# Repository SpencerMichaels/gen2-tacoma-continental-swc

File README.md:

# Gen 2 Tacoma → Continental steering-wheel controls

A small board that lets the steering-wheel audio buttons of a **second-generation Toyota Tacoma** (2005–2015) control a **Continental CRD4512UBA** aftermarket radio.

The Tacoma's wheel buttons and the Continental's steering-wheel input both use resistance, but they aren't compatible. The truck splits its seven buttons across two wires (SW1 and SW2), with resistances of about 0 Ω, 330 Ω, 1 kΩ and 3.1 kΩ on each. The radio reads a single wire and recognises a different set of resistance ranges, from 0–100 Ω for Volume Down to 1.3–3 kΩ for Mic Mute. This board reads the truck's two lines, works out which button is pressed, and switches in the resistance the radio wants for that command.

*3D render, seen from the connector edge. J1 (grey) is a simplified stand-in model. The XIAO module itself isn't shown, only its two sockets.*

## How it works

- **Inputs.** Each wheel line (SW1, SW2) is pulled up to 3.3 V through 2.2 kΩ. Pressing a button connects a resistor from the line to ground, and the voltage drops by a predictable amount. The XIAO RP2040 reads both lines with its 12-bit ADC about every 2 ms.
- **Decoding.** Each reading falls into a band: released, or one of the buttons. Readings between bands, or both lines active at once, are treated as invalid and the output is released. A press has to hold steady for 20 ms before it counts.
- **Outputs.** Five resistors (47 Ω, 191 Ω, 390 Ω, 1 kΩ, 2 kΩ) sit between the radio's SWRC+ and SWRC GND, each switched by its own MOSFET. Five of the seven commands use one resistor; Volume + and Seek + use two in parallel, switched on together in a single register write. While you hold a button, the board holds the resistance; the radio handles its own repeat.
- **Power.** The board runs from the truck's switched 12 V ACC through a fuse, a reverse-polarity diode, a 10 Ω resistor, a TVS diode and an LT3012 regulator set to 5 V. It draws about 25 mA. The radio supplies its own sense voltage, so the board never drives the radio input; it only presents a resistance.
- **Fail-safe.** Gate pull-downs hold every output off through reset or with the XIAO unplugged. A 1-second watchdog restarts a stalled loop, and a press held longer than 10 seconds is released.

| Wheel button | Line | Radio command | Board output |
|---|---|---|---:|
| Seek + | SW1 | Seek Up | 390 Ω ‖ 1 kΩ = 281 Ω |
| Seek − | SW1 | Seek Down | 390 Ω |
| Volume + | SW1 | Volume Up | 191 Ω ‖ 390 Ω = 128 Ω |
| Volume − | SW1 | Volume Down | 47 Ω |
| Mode | SW2 | Source | 191 Ω |
| Answer (off-hook) | SW2 | Phone (answers, or ends an active call) | 1 kΩ |
| Hang Up (on-hook) | SW2 | Mic Mute | 2 kΩ |

The radio's Phone command toggles with the call state, so Answer covers both answering and hanging up. That frees the Hang Up button for Mic Mute. The radio has a Preset command (470–720 Ω) that isn't mapped to any button.

The wheel resistances, the radio's measured recognition windows and the harness wiring are in [docs/interface.md](docs/interface.md).

## Status

**Built and working on the bench.** Two boards were made with factory assembly. On a powered CRD4512UBA, every command acted once per press: Volume Up/Down, Source, Seek Up/Down, Mic Mute (toggled on and off during a call), and Phone (ended a connected call). Powered from 12 V ACC, the board draws 25 mA and the regulator stays cool.

The ADC bands for the wheel buttons come from the Toyota service-manual resistances and circuit simulation, not from readings on the truck. If a button misbehaves in your truck, send `status` over USB while holding it, and compare the count with the bands in [firmware/README.md](firmware/README.md).

Tested with a 2013 Tacoma. The wheel resistances are documented for 2011–2015 trucks; earlier Gen 2 trucks with audio buttons probably match, but measure them first.

## Building one

1. **Order the assembled board.** The regulator (LT3012, 3 × 4 mm DFN) and most of the parts are surface-mount, so a PCB assembly service is the practical route. Upload [`hardware/fab/tacoma_swc_gerbers.zip`](hardware/fab/tacoma_swc_gerbers.zip), [`BOM.csv`](hardware/fab/BOM.csv) and [`smt-placement.csv`](hardware/fab/assembly/smt-placement.csv). See the [ordering notes](hardware/fab/ORDERING.md).
2. **Get a XIAO RP2040** (the standard one, not the Plus) with its 1 × 7 male headers soldered on. It plugs into two sockets on the carrier.
3. **Load the firmware.** Pull the **JP1** shunt first, then hold the XIAO's BOOT button while plugging in USB and copy a UF2 file onto the drive that appears: [`tacoma-swc-bench.uf2`](firmware/releases/tacoma-swc-bench.uf2) to test from a computer, or [`tacoma-swc-vehicle.uf2`](firmware/releases/tacoma-swc-vehicle.uf2) for the truck. Details in [firmware/README.md](firmware/README.md).
4. **Test on the bench (optional).** With the bench build, USB serial commands like `volume_up` pulse the matching output for 300 ms. Connect J1 pin 9 (SWRC+) and pin 10 (SWRC GND) to the radio and check each one.
5. **Print the case** (PETG or ASA) from [`hardware/enclosure/`](hardware/enclosure/): two parts, no supports, 4 × M3 × 12 screws, no nuts.

6. **Install.** Load the vehicle build, **refit JP1**, plug the harness into J1, and set the radio's SWRC type to *Resistance*.

## Wiring

J1 is a Molex Micro-Fit 3.0, 2 × 6 right-angle header (43045-1209). It mates with the 12-pin harness of an Axxess AXSWC steering-wheel interface, so the board can take the AXSWC's place. You don't need the AXSWC module itself, only its harness:

- **Alternative:** the [RED WOLF 20-pin steering-wheel control harness w/RCA](https://www.amazon.com/RED-WOLF-Replacement-2003-2014-Aftermarket/dp/B09S33B8L1). It's sold separately as a replacement harness for the AXSWC/ASWC-1, so it has the same 12-pin plug and pinout. It should work as-is, though it hasn't been tried with this board yet.
- **Make your own:** a Molex 43025-1200 housing and Micro-Fit crimp terminals.

| J1 pin | Signal | Goes to |
|---:|---|---|
| 4 | SW1 | Tacoma radio connector R15-21 (wheel ladder 1) |
| 8 | SW2 | Tacoma R15-22 (wheel ladder 2) |
| 6 | GND | Vehicle ground, tied to the wheel's SWG (R15-23) |
| 12 | ACC | Switched 12 V |
| 9 | SWRC+ | Radio steering-wheel input, 3.5 mm plug tip (red) |
| 10 | SWRC GND | Radio steering-wheel ground (white) |
| others | — | Not connected |

Test points: TP1 GND, TP2 5 V regulator output, TP3 SWRC+, TP4 SWRC GND, TP5 ACC after protection, TP6 XIAO 5 V, TP7/TP8 SW1/SW2 at the ADC, TP9 3.3 V.

## Safety notes

- **Pull JP1 before plugging in USB.** The XIAO's 5 V pin is wired straight to its USB VBUS. With JP1 fitted, the board's regulator and the computer's USB port would be connected together. The silkscreen says so too.
- Don't measure the board's output resistance with an ohmmeter while the radio is connected and powered. Watch what the radio does instead.
- The power input is fused, reverse-protected and clamped (24 V TVS), but it hasn't been qualified against automotive load-dump or jump-start tests.
- Don't wrap the case in harness tape; leave the vented side and the top open.

## Repository layout

| Path | What |
|---|---|
| [`hardware/`](hardware/) | KiCad 10 project, design checks, SPICE simulation and the generator scripts. [Design notes](hardware/README.md). |
| [`hardware/fab/`](hardware/fab/) | Gerbers, BOM, placement files, assembly drawings, [ordering notes](hardware/fab/ORDERING.md) |
| [`hardware/enclosure/`](hardware/enclosure/) | Case STLs and STEP, plus the FreeCAD generator script |
| [`firmware/`](firmware/) | RP2040 firmware (PlatformIO + Arduino-Pico), prebuilt UF2 files, host tests |
| [`docs/interface.md`](docs/interface.md) | The Tacoma wheel ladders, the Continental input, and the harness |

## License

- **Hardware** (everything under `hardware/` except the Python scripts: schematic, PCB, Gerbers, BOM, case models): [CERN-OHL-S-2.0](LICENSE-HARDWARE).
- **Firmware, scripts and tools:** [GPL-3.0](LICENSE).
- **Documentation:** follows the hardware or software it describes.

## Credits

- Steering-wheel resistances come from the 2013 Tacoma repair manual: *Navigation System (Diagnostic Codes & Symptom Tests) → Symptom Tests → Steering Pad Switch Circuit → Procedure*. The harness and switch-assembly resistance tables are under Figures 45 and 46. [docs/interface.md](docs/interface.md#tacoma-steering-wheel) has the full citation.
- The XIAO socket footprint follows Seeed Studio's [KiCad library](https://github.com/Seeed-Studio/OPL_Kicad_Library).
- Built with KiCad, Freerouting, ngspice, FreeCAD, PlatformIO and the [Arduino-Pico](https://github.com/earlephilhower/arduino-pico) core.

Toyota and Tacoma are trademarks of Toyota Motor Corporation. Continental is a trademark of its owner. Axxess is a trademark of Metra Electronics. XIAO is a trademark of Seeed Technology. This project isn't affiliated with or endorsed by any of them.

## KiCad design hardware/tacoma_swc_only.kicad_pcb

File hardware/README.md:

# Hardware

The KiCad 10 project for the SWC board: 65 × 55 mm, 2 layers, 1.6 mm FR-4, ENIG, all components on the top side. Most parts are SMT and meant for factory assembly; the XIAO RP2040 plugs into two sockets.

| File | What |
|---|---|
| `tacoma_swc_only.kicad_pro` / `.kicad_sch` / `.kicad_pcb` | The KiCad project, with four schematic sheets: interface, power, inputs, outputs |
| `fab/` | Gerbers, BOM, placement files, assembly drawings, [ordering notes](fab/ORDERING.md) |
| `enclosure/` | 3D-printable case: STL, STEP and the generator; see its [README](enclosure/README.md) |
| `checks/` | Schematic PDF, layout PDF, top/bottom SVGs, ERC/DRC reports, design-check results, netlist, simulation outputs |
| `design_intent.json`, `output_commands.json`, `parts_selection.json` | Machine-readable pin, net, command and part data that the scripts and firmware tests check against |
| `build_schematic.py`, `build_board.py`, `clean_route_stubs.py`, `check_design.py` | Scripts that generate and check the design (see [Rebuilding](#rebuilding)) |
| `simulation/`, [`simulation_review.md`](simulation_review.md) | ngspice checks of the inputs, outputs, command transitions and layout spacing |
| `footprints/`, `Tacoma.kicad_sym` | Project footprint and symbol libraries |
| `3dmodels/` | Simplified Micro-Fit (J1) model and its generator, since KiCad's library has none |

**Status.** This is the board that was built: the PCB file's SHA-256 was `6188309d…cdaf1a` when it was fabricated. Since then only the 3D model references for J1 and A1 have changed, so copper, DRC and Gerbers are the same. It passes ERC (0 violations) and DRC with schematic parity (0 violations, 0 unconnected, 0 parity errors). Two factory-assembled boards were bench-tested with the radio; see the [main README](../README.md#status).

## Circuit

| Block | Parts | What it does |
|---|---|---|
| **Power input** | F1 250 mA fast fuse, D1 STPS1H100A, R1 10 Ω 1 W, D2 SMBJ24A, C1 47 µF/63 V, C2 10 µF/63 V | ACC → fuse → reverse-blocking Schottky → 10 Ω → TVS clamp. R1 limits the current the TVS has to absorb. |
| **Regulator** | U1 LT3012EDE (DFN-12), R2 30.1 k / R3 10.0 k (0.1 %), C3 22 µF polymer | 5 V nominal (4.97 V). The LT3012 tolerates reverse input and up to 80 V. The output goes to the XIAO's 5 V pin through JP1. |
| **JP1** | 2-pin header + shunt | Disconnects the regulator from the XIAO. **Pull it before connecting USB**: the XIAO's 5 V pin is tied directly to USB VBUS. |
| **Wheel inputs** | D5/D6 BAS70, R5/R6 2.2 kΩ, R7/R8 22 kΩ, C5/C6 10 nF, D7/D8 BAS70-04, R4 330 Ω | Each line is pulled up from the XIAO's 3.3 V through a diode and 2.2 kΩ. The 22 kΩ + 10 nF filter and the clamp diodes protect the ADC pin. R4 bleeds 3.3 V so that small clamp currents can't lift the rail. |
| **Outputs** | Q1/Q3/Q5/Q6/Q7 AO3400A, R11 47 Ω, R13 191 Ω, R15 390 Ω, R16 1 kΩ, R17 2 kΩ (1 %), 1 kΩ gate resistors, 100 kΩ gate pull-downs | Five low-side branches from SWRC+ to SWRC GND. The pull-downs keep every branch off while the XIAO is in reset or unplugged. |
| **C11** | 10 nF | Across SWRC+ / SWRC GND. Softens the switching edges. |
| **NT1** | net tie | Bonds SWRC GND to the board ground. |

### XIAO pins

The firmware uses RP2040 GPIO numbers, not the XIAO's D labels.

| Carrier pad | XIAO label | RP2040 | Function |
|---:|---|---|---|
| 1 | D0 | GP26 / ADC0 | SW1 |
| 2 | D1 | GP27 / ADC1 | SW2 |
| 7 | D6 | GP0 | 47 Ω branch (Q1) |
| 8 | D7 | GP1 | 191 Ω branch (Q3) |
| 9 | D8 | GP2 | 390 Ω branch (Q5) |
| 10 | D9 | GP4 | 1 kΩ branch (Q6) |
| 11 | D10 | GP3 | 2 kΩ branch (Q7) |
| 12 | 3V3 | | Pull-up and clamp supply (from the XIAO's own regulator) |
| 13 | GND | | |
| 14 | 5V | | From JP1 |
| 3–6 | D2–D5 | | Not used |

Pads are numbered DIP-style: viewed from above with USB at the top, 1–7 run down the left side and 8–14 run up the right.

### Command masks

| Command | Branches | Ω | GPIO mask |
|---|---|---:|---:|
| Release | none | open | `0x00` |
| Volume Down | Q1 | 47 | `0x01` |
| Volume Up | Q3 + Q5 | 128.2 | `0x06` |
| Source | Q3 | 191 | `0x02` |
| Seek Up | Q5 + Q6 | 280.6 | `0x14` |
| Seek Down | Q5 | 390 | `0x04` |
| Phone | Q6 | 1000 | `0x10` |
| Mic Mute | Q7 | 2000 | `0x08` |

## Power budget

| | |
|---|---|
| Measured, 12 V ACC, XIAO running, no USB | 25 mA total |
| Measured, 12 V ACC, XIAO removed | under 1 mA |
| Design allocation | 60 mA |
| U1 dissipation at 16 V, 25 mA | about 0.3 W (U1 plus R1) |

At the measured current, U1, C3 and R1 aren't noticeably warm. The case has vents over U1 and R1 anyway.

## PCB layout

- **Placement.** J1 is on the top edge, and the XIAO sits on the left with its USB port facing up. The output bank runs along the bottom, and the power section is on the right. There's an M3 mounting hole in each corner, with a 7 × 7 mm copper keep-out around each.
- **Routing.** Freerouting, imported into KiCad and cleaned up. Signals are 0.3 mm; ACC and the SWRC return are 0.6 mm. There are ground pours on both layers. U1's exposed pad has four ground vias.
- **ACC spacing.** `tacoma_swc_only.kicad_dru` keeps at least 2 mm between every ACC net and SWRC+ or the output-branch nets; the layout gives about 2.15 mm. So a stray solder bridge is unlikely to put 12 V on the radio's input.
- **XIAO sockets.** The two Samtec SSW-107-01-G-S sockets are 15.24 mm apart in 1.04 mm finished holes. Nothing on the carrier sits under the module.
- **3D models.**
  - J1 uses `3dmodels/Molex_Micro-Fit_3.0_43045-1210_simplified.step`, generated by `3dmodels/make_microfit_model.py`.
  - A1 uses two of KiCad's `PinSocket_1x07_P2.54mm_Vertical` models. There's no model of the XIAO module itself.

## Simulation

`simulation/run_simulation.py` builds ngspice circuits from the KiCad netlist. Results are in `checks/simulation/`, and the summary is in [`simulation_review.md`](simulation_review.md). The checks cover:

- **Input bands:** every wheel resistance over the tolerance sweep lands in its own band.
- **Outputs:** every command lands inside its Continental window.
- **Transitions:** all 56 command-to-command changes, at two C11 values (`check_command_transitions.py`).
- **Firmware:** 3,024 cases with the real C++ decoder driven by simulated ADC waveforms, including bounce and RC settling (`check_firmware_integration.py`).
- **Faults:** an ACC bridge onto SWRC+, and a drain-source short.

The MCU and radio are modelled as simple stubs, so these results show the design is consistent, not that it survives every fault.

## Rebuilding

Run from the repository root:

```sh
KPY=/Applications/KiCad/KiCad.app/Contents/Frameworks/Python.framework/Versions/Current/bin/python3

python3 hardware/check_design.py                             # pin/net/part checks → checks/design_checks.json
python3 hardware/simulation/run_simulation.py                # ngspice (needs ngspice on PATH)
python3 hardware/simulation/check_command_transitions.py
python3 hardware/simulation/check_firmware_integration.py
$KPY hardware/simulation/audit_layout.py                     # ACC spacing audit

kicad-cli sch erc --format json -o hardware/checks/erc.json hardware/tacoma_swc_only.kicad_sch
kicad-cli pcb drc --schematic-parity --format json -o hardware/checks/pcb-drc.json hardware/tacoma_swc_only.kicad_pcb
```

`build_schematic.py` and `build_board.py` generated the original schematic and placement. **Re-running them overwrites the KiCad files**, including the routing. Edit the KiCad files directly instead, unless you mean to start over.

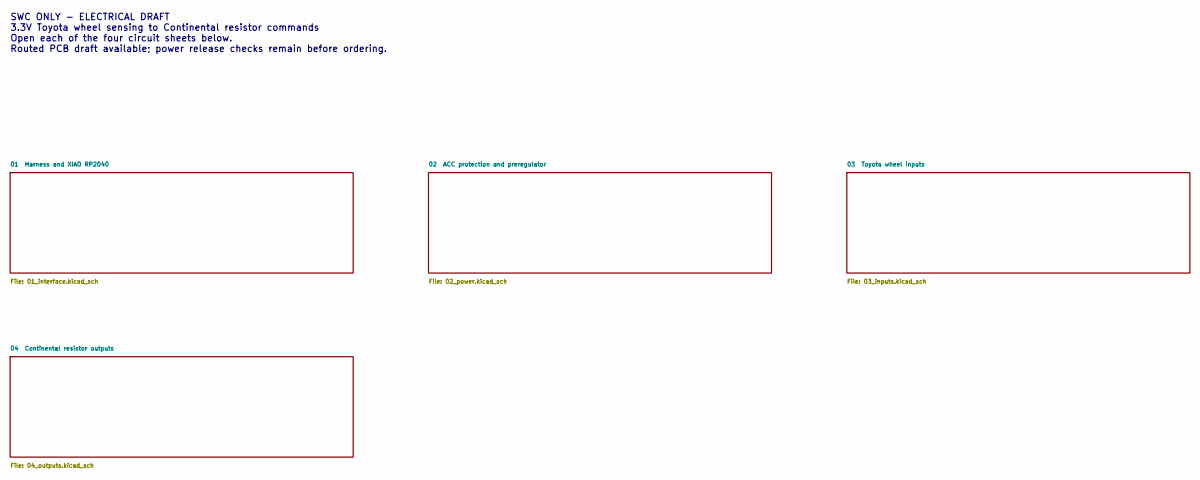
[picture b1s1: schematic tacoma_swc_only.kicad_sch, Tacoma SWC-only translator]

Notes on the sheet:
SWC ONLY - ELECTRICAL DRAFT 3.3V Toyota wheel sensing to Continental resistor commands Open each of the four circuit sheets below. Routed PCB draft available; power release checks remain before ordering.

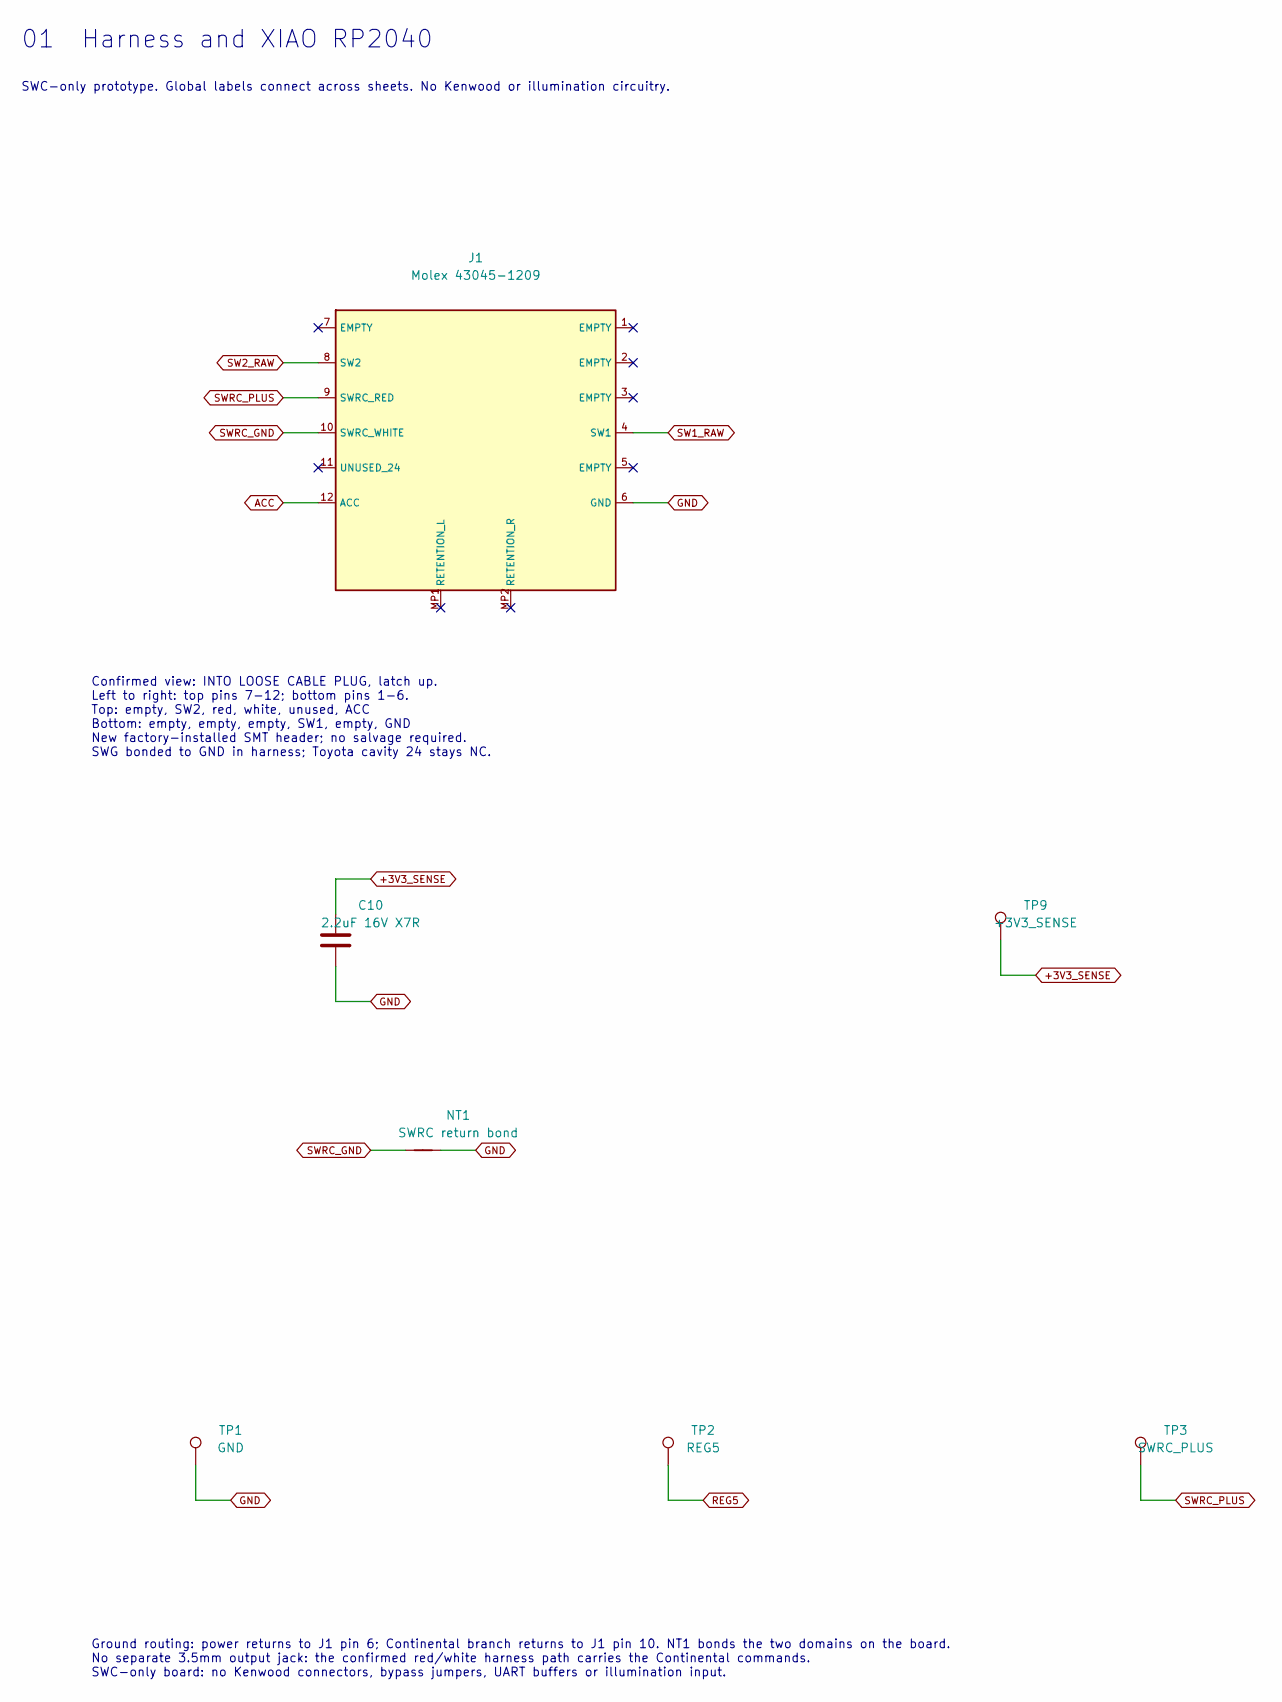
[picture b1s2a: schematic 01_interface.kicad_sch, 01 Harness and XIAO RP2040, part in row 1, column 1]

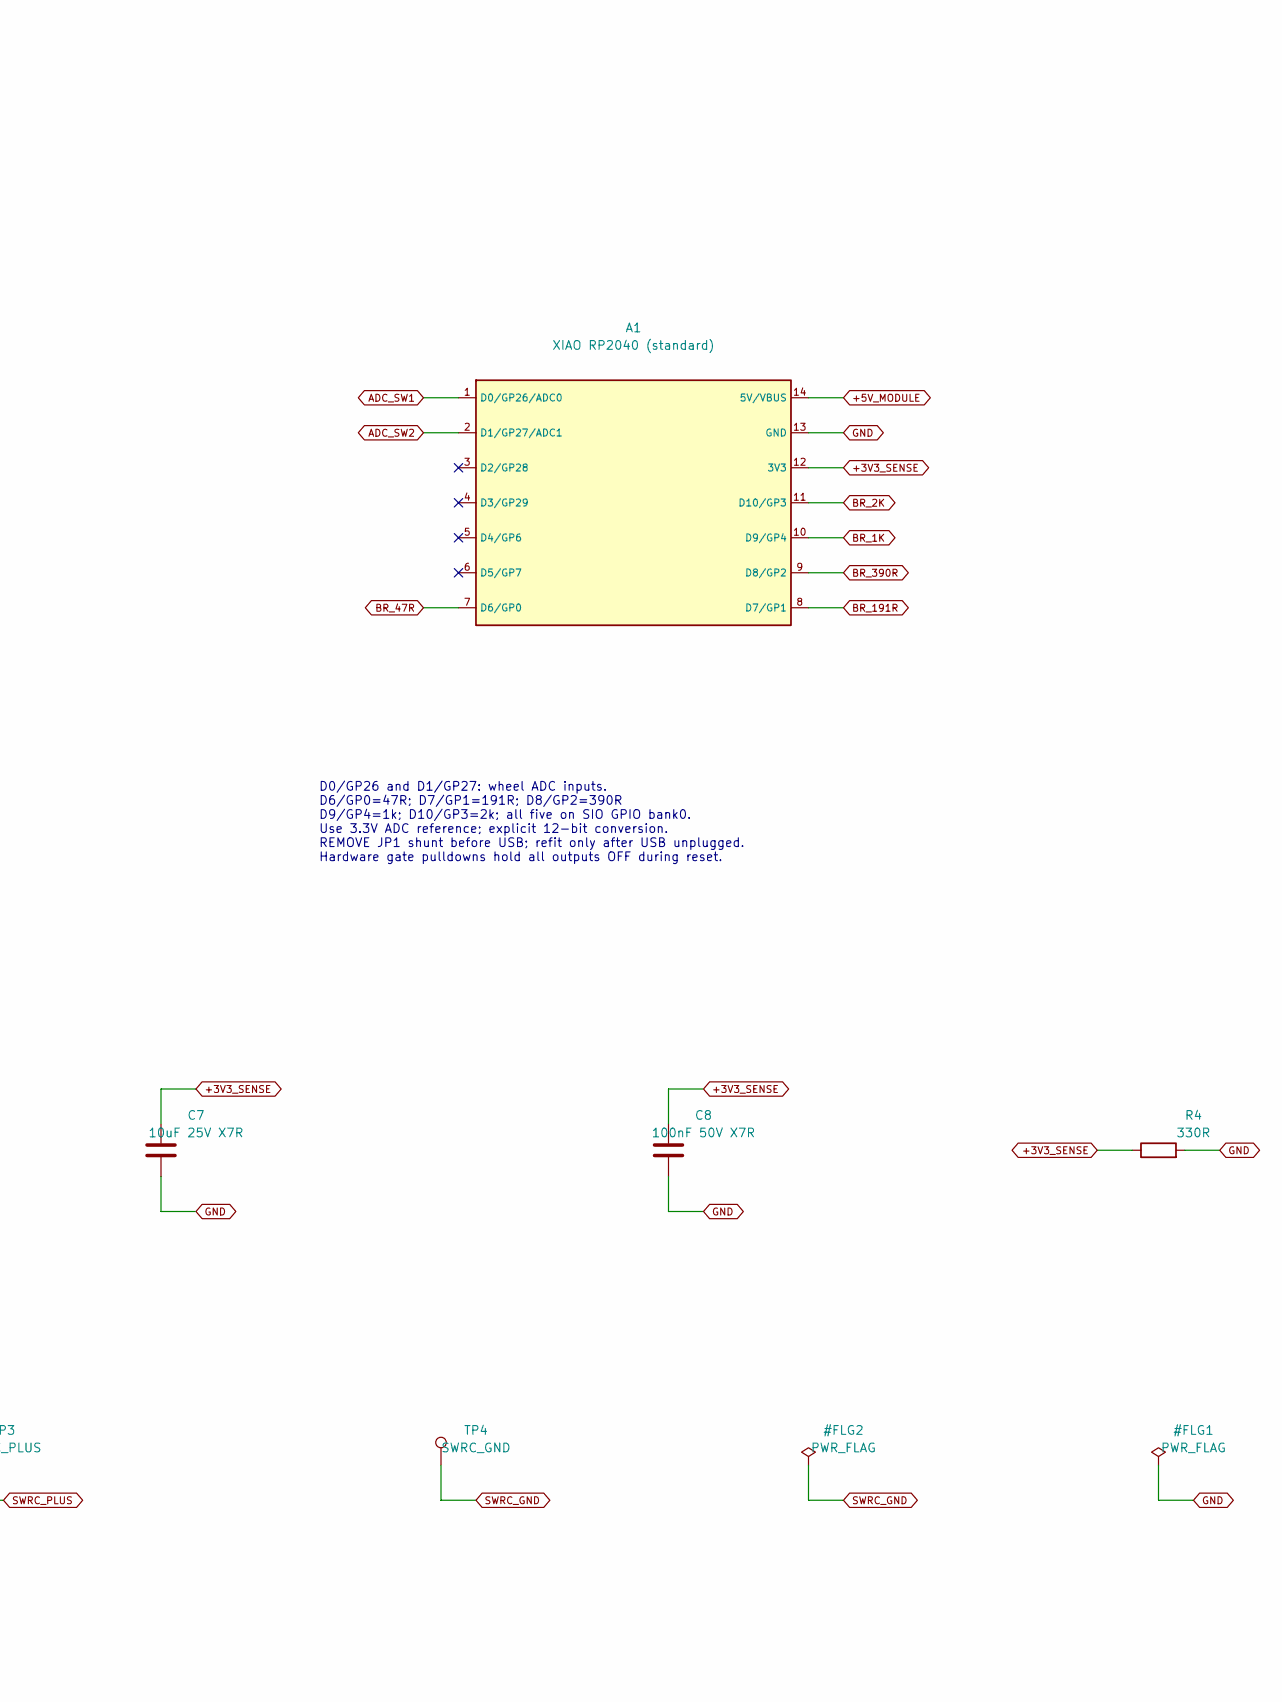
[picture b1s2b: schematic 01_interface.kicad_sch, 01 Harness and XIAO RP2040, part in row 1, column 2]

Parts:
A1: XIAO RP2040 (standard); XIAO_RP2040_Socket_2x7; MPN 102010428
C7: 10uF 25V X7R; C_1206_3216Metric; MPN GRM31CR71E106KA12L
C8: 100nF 50V X7R; C_0805_2012Metric; MPN C0805C104K5RACTU
C10: 2.2uF 16V X7R; C_0805_2012Metric; MPN GRM21BR71C225KA12L
J1: Molex 43045-1209; Molex_43045_12_SMT_SeparateRetentionPads; MPN 43045-1209
NT1: SWRC return bond; NetTie-2_SMD_Pad2.0mm
R4: 330R; R_1206_3216Metric; MPN RC1206FR-07330RL
TP1: GND; TestPoint_Pad_D1.5mm
TP2: REG5; TestPoint_Pad_D1.5mm
TP3: SWRC_PLUS; TestPoint_Pad_D1.5mm
TP4: SWRC_GND; TestPoint_Pad_D1.5mm
TP9: +3V3_SENSE; TestPoint_Pad_D1.5mm

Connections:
+3V3_SENSE: A1.12 (3V3), C7.1, C8.1, C10.1, R4.1, TP9.1; also elsewhere on the board
+5V_MODULE: A1.14 (5V/VBUS); also elsewhere on the board
ACC: J1.12 (ACC); also elsewhere on the board
ADC_SW1: A1.1 (D0/GP26/ADC0); also elsewhere on the board
ADC_SW2: A1.2 (D1/GP27/ADC1); also elsewhere on the board
BR_1K: A1.10 (D9/GP4); also elsewhere on the board
BR_2K: A1.11 (D10/GP3); also elsewhere on the board
BR_47R: A1.7 (D6/GP0); also elsewhere on the board
BR_191R: A1.8 (D7/GP1); also elsewhere on the board
BR_390R: A1.9 (D8/GP2); also elsewhere on the board
GND: A1.13 (GND), C7.2, C8.2, C10.2, J1.6 (GND), NT1.2, R4.2, TP1.1; also elsewhere on the board
REG5: TP2.1; also elsewhere on the board
SW1_RAW: J1.4 (SW1); also elsewhere on the board
SW2_RAW: J1.8 (SW2); also elsewhere on the board
SWRC_GND: J1.10 (SWRC_WHITE), NT1.1, TP4.1; also elsewhere on the board
SWRC_PLUS: J1.9 (SWRC_RED), TP3.1; also elsewhere on the board

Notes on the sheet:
01 Harness and XIAO RP2040
SWC-only prototype. Global labels connect across sheets. No Kenwood or illumination circuitry.
Confirmed view: INTO LOOSE CABLE PLUG, latch up. Left to right: top pins 7-12; bottom pins 1-6. Top: empty, SW2, red, white, unused, ACC Bottom: empty, empty, empty, SW1, empty, GND New factory-installed SMT header; no salvage required. SWG bonded to GND in harness; Toyota cavity 24 stays NC.
D0/GP26 and D1/GP27: wheel ADC inputs. D6/GP0=47R; D7/GP1=191R; D8/GP2=390R D9/GP4=1k; D10/GP3=2k; all five on SIO GPIO bank0. Use 3.3V ADC reference; explicit 12-bit conversion. REMOVE JP1 shunt before USB; refit only after USB unplugged. Hardware gate pulldowns hold all outputs OFF during reset.
Ground routing: power returns to J1 pin 6; Continental branch returns to J1 pin 10. NT1 bonds the two domains on the board. No separate 3.5mm output jack: the confirmed red/white harness path carries the Continental commands. SWC-only board: no Kenwood connectors, bypass jumpers, UART buffers or il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

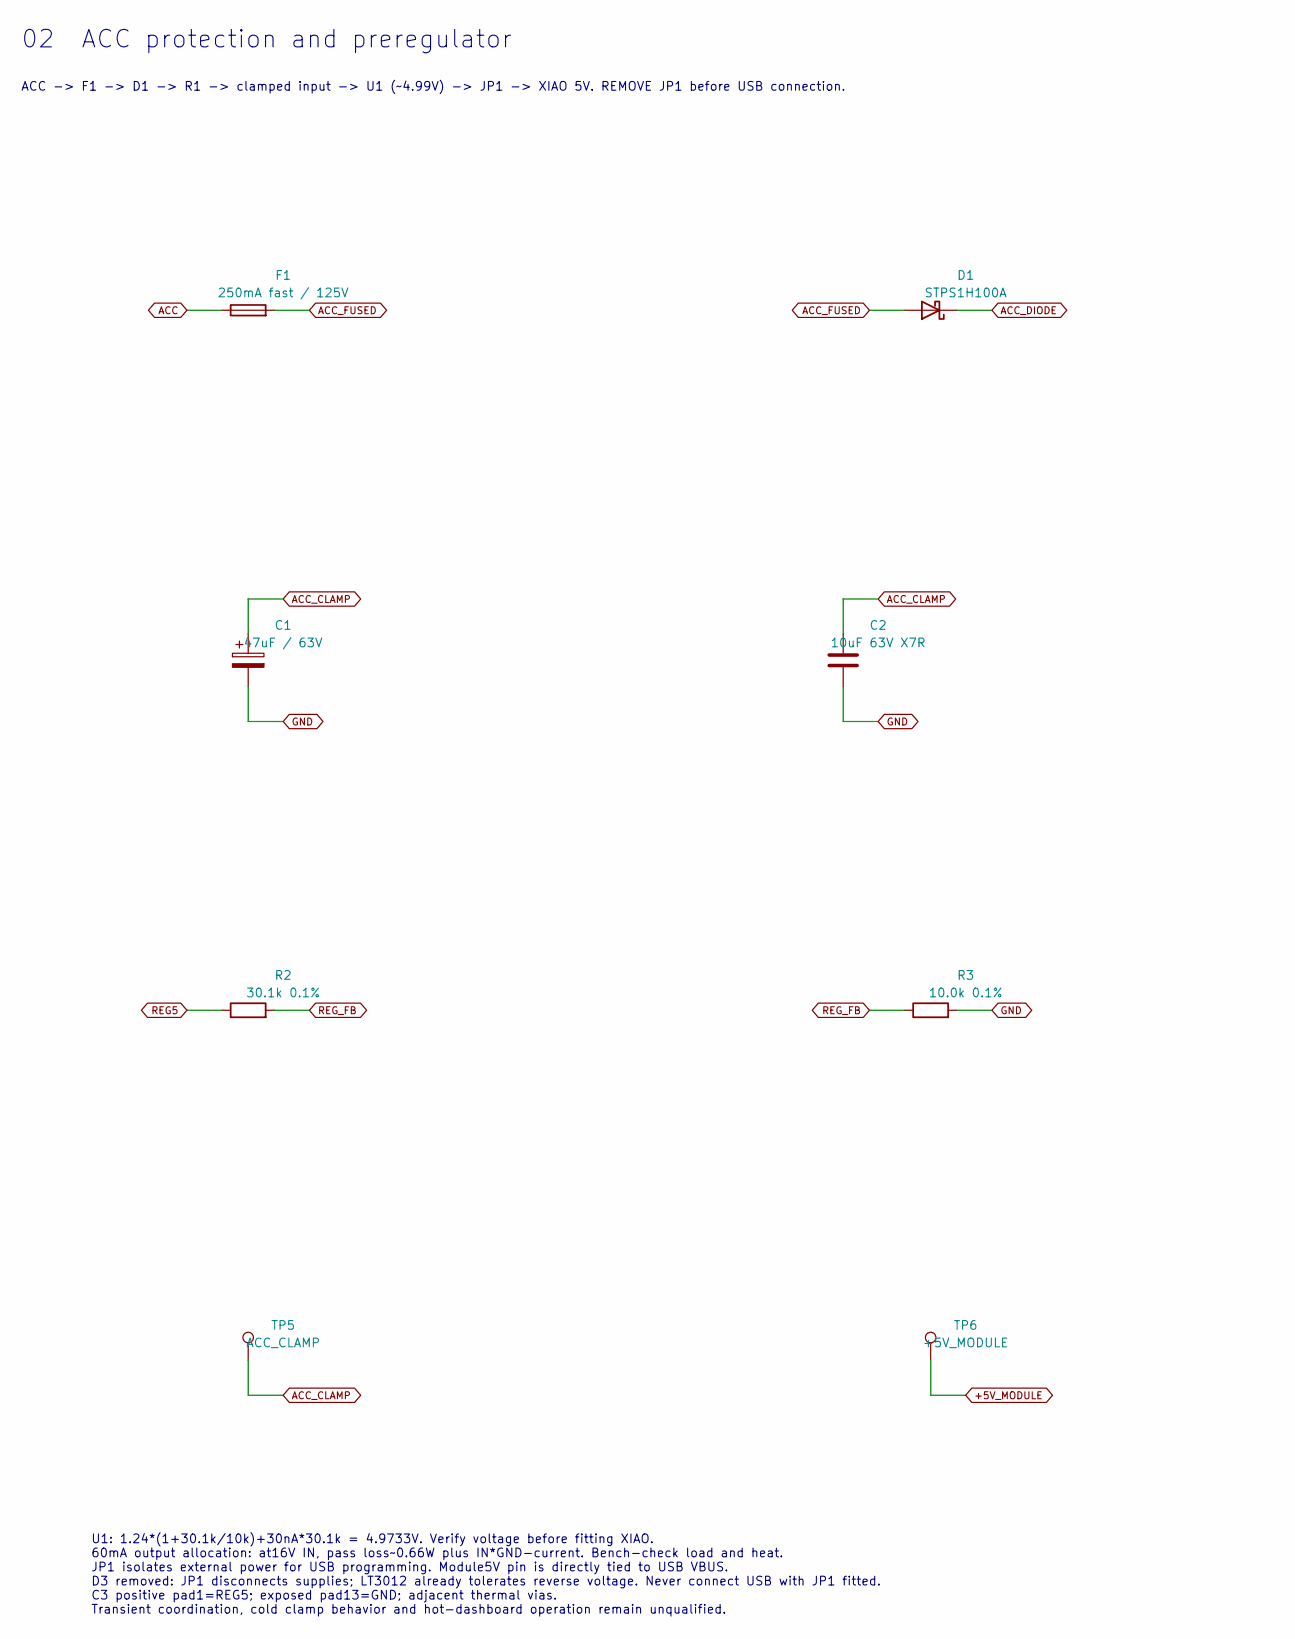
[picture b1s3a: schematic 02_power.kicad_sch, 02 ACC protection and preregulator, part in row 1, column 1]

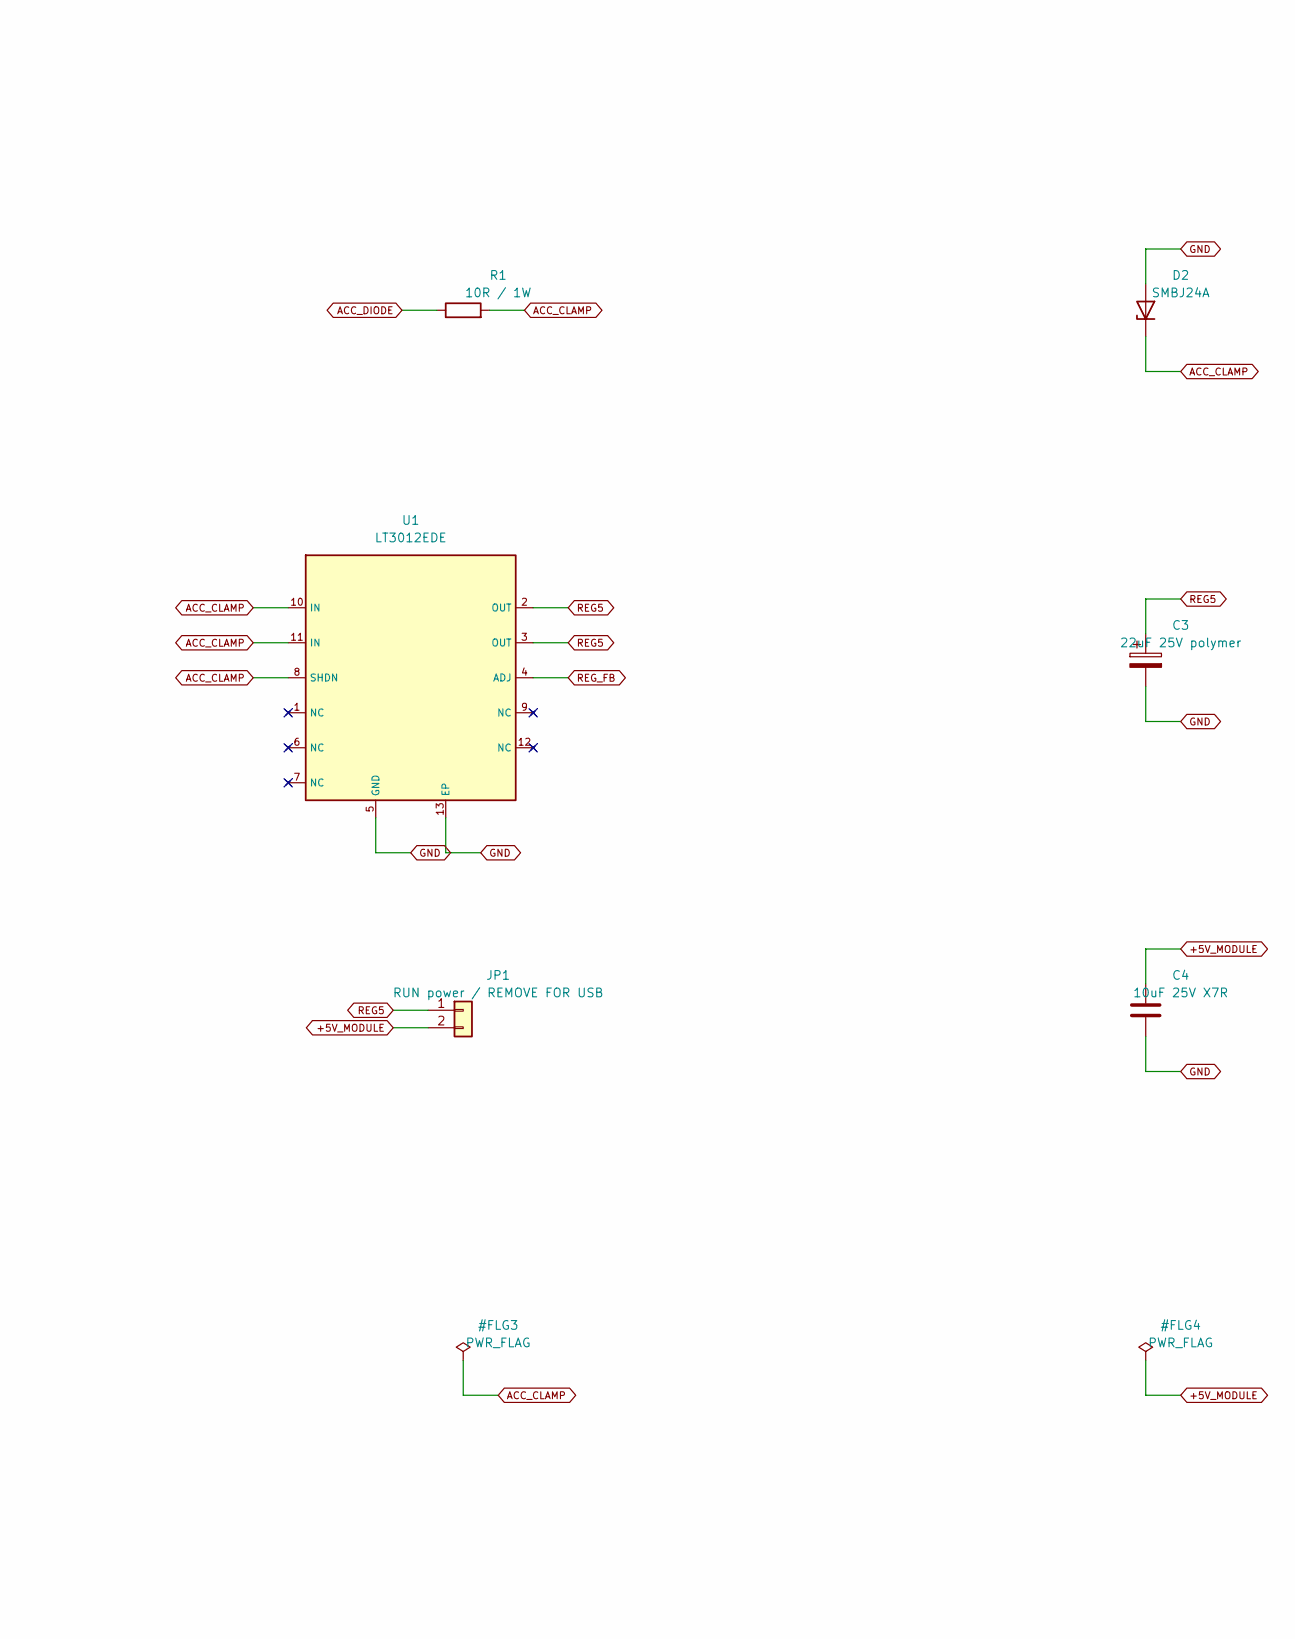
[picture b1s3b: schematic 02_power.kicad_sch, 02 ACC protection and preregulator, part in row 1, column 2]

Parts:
C1: 47uF / 63V; CP_Elec_8x10.5; MPN EEE-FK1J470P
C2: 10uF 63V X7R; C_1210_3225Metric; MPN GRM32ER71J106KA12L
C3: 22uF 25V polymer; CP_EIA-3528-21_Kemet-B; MPN TCJB226M025R0100E
C4: 10uF 25V X7R; C_1206_3216Metric; MPN GRM31CR71E106KA12L
D1: STPS1H100A; D_SMA; MPN STPS1H100A
D2: SMBJ24A; D_SMB; MPN SMBJ24A
F1: 250mA fast / 125V; Littelfuse_451_6.1x2.69mm; MPN 0451.250MRL
JP1: RUN power / REMOVE FOR USB; PinHeader_1x02_P2.54mm_Vertical; MPN TSW-102-07-G-S
R1: 10R / 1W; R_Axial_DIN0414_L11.9mm_D4.5mm_P20.32mm_Horizontal; MPN AC01000001009JA100
R2: 30.1k 0.1%; R_0805_2012Metric; MPN RT0805BRD0730K1L
R3: 10.0k 0.1%; R_0805_2012Metric; MPN RT0805BRD0710KL
TP5: ACC_CLAMP; TestPoint_Pad_D1.5mm
TP6: +5V_MODULE; TestPoint_Pad_D1.5mm
U1: LT3012EDE; DFN-12-1EP_3x4mm_P0.5mm_EP1.7x3.3mm; MPN LT3012EDE#WPBF

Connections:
+5V_MODULE: C4.1, JP1.2, TP6.1; also elsewhere on the board
ACC: F1.1; also elsewhere on the board
ACC_CLAMP: C1.1, C2.1, D2.1 (K), R1.2, TP5.1, U1.8 (SHDN), U1.10 (IN), U1.11 (IN)
ACC_DIODE: D1.1 (K), R1.1
ACC_FUSED: D1.2 (A), F1.2
GND: C1.2, C2.2, C3.2, C4.2, D2.2 (A), R3.2, U1.5 (GND), U1.13 (EP); also elsewhere on the board
REG5: C3.1, JP1.1, R2.1, U1.2 (OUT), U1.3 (OUT); also elsewhere on the board
REG_FB: R2.2, R3.1, U1.4 (ADJ)

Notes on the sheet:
02 ACC protection and preregulator
ACC -> F1 -> D1 -> R1 -> clamped input -> U1 (~4.99V) -> JP1 -> XIAO 5V. REMOVE JP1 before USB connection.
U1: 1.24*(1+30.1k/10k)+30nA*30.1k = 4.9733V. Verify voltage before fitting XIAO. 60mA output allocation: at16V IN, pass loss~0.66W plus IN*GND-current. Bench-check load and heat. JP1 isolates external power for USB programming. Module5V pin is directly tied to USB VBUS. D3 removed: JP1 disconnects 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

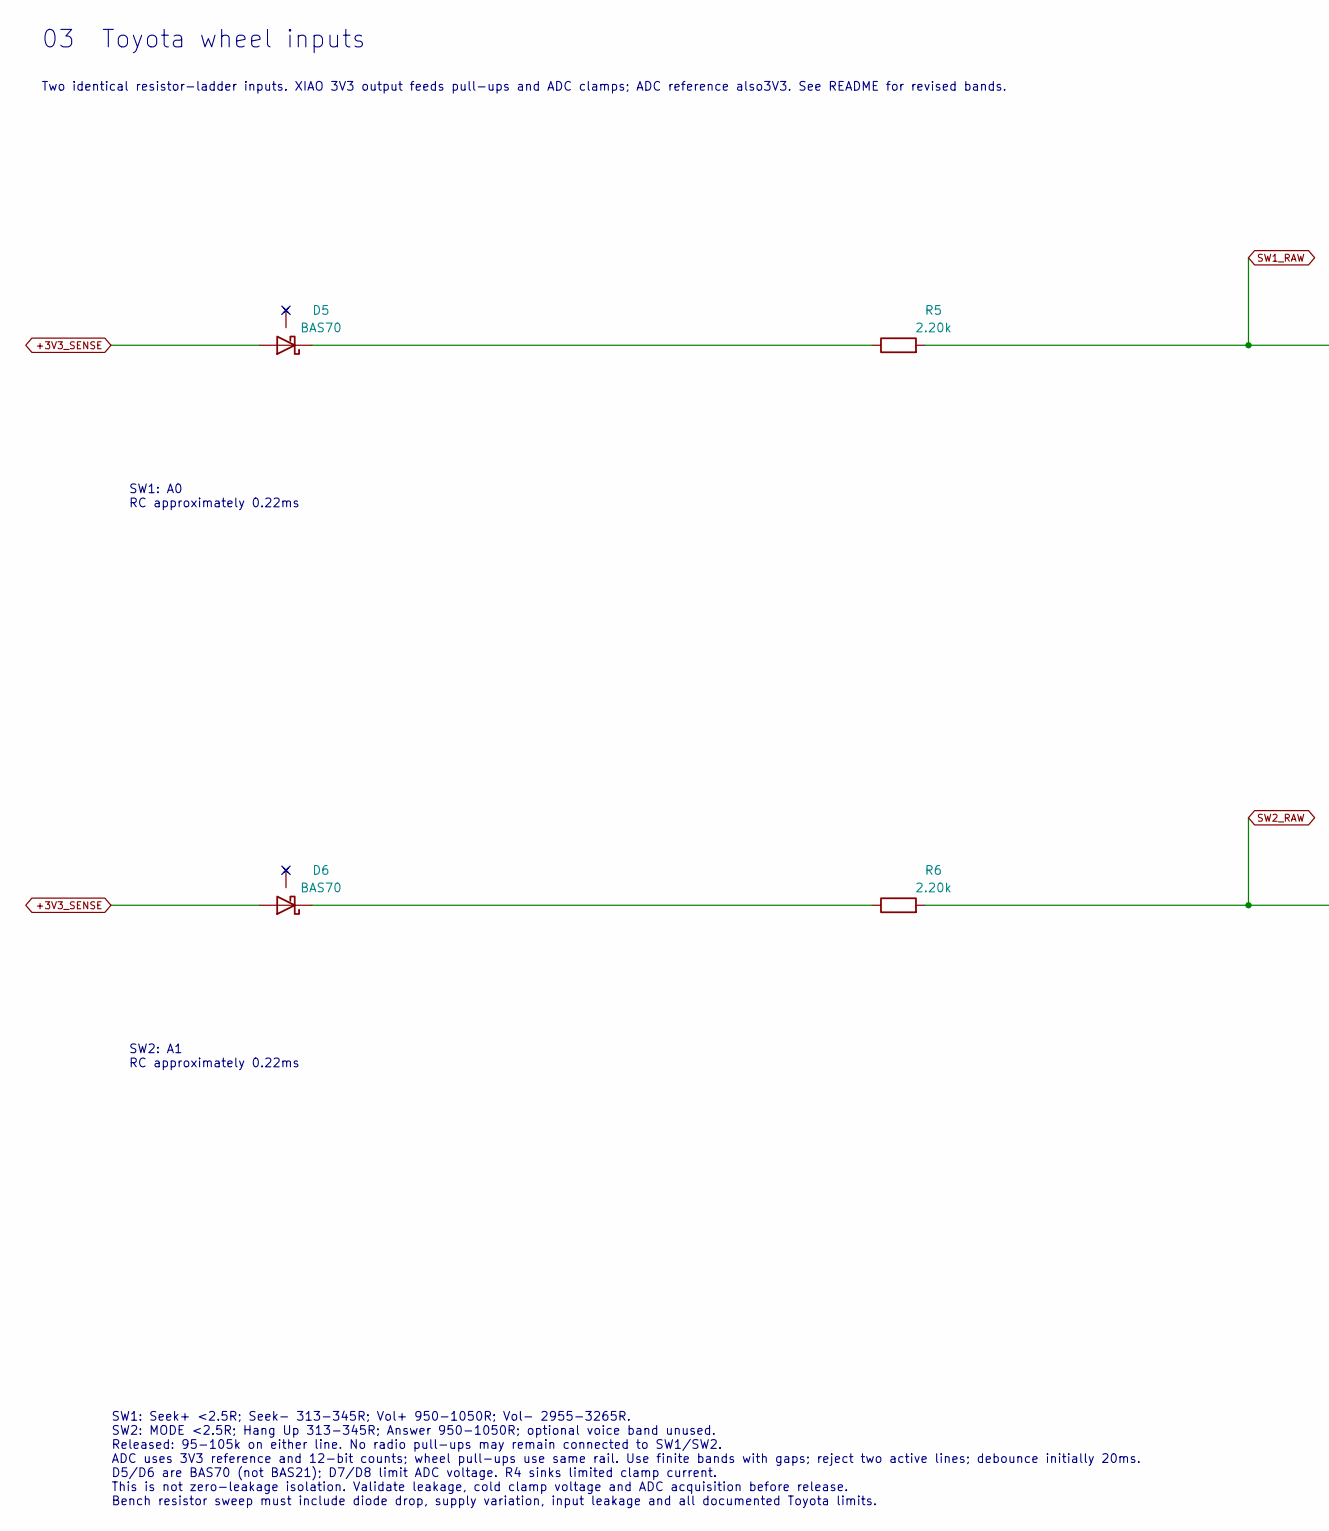
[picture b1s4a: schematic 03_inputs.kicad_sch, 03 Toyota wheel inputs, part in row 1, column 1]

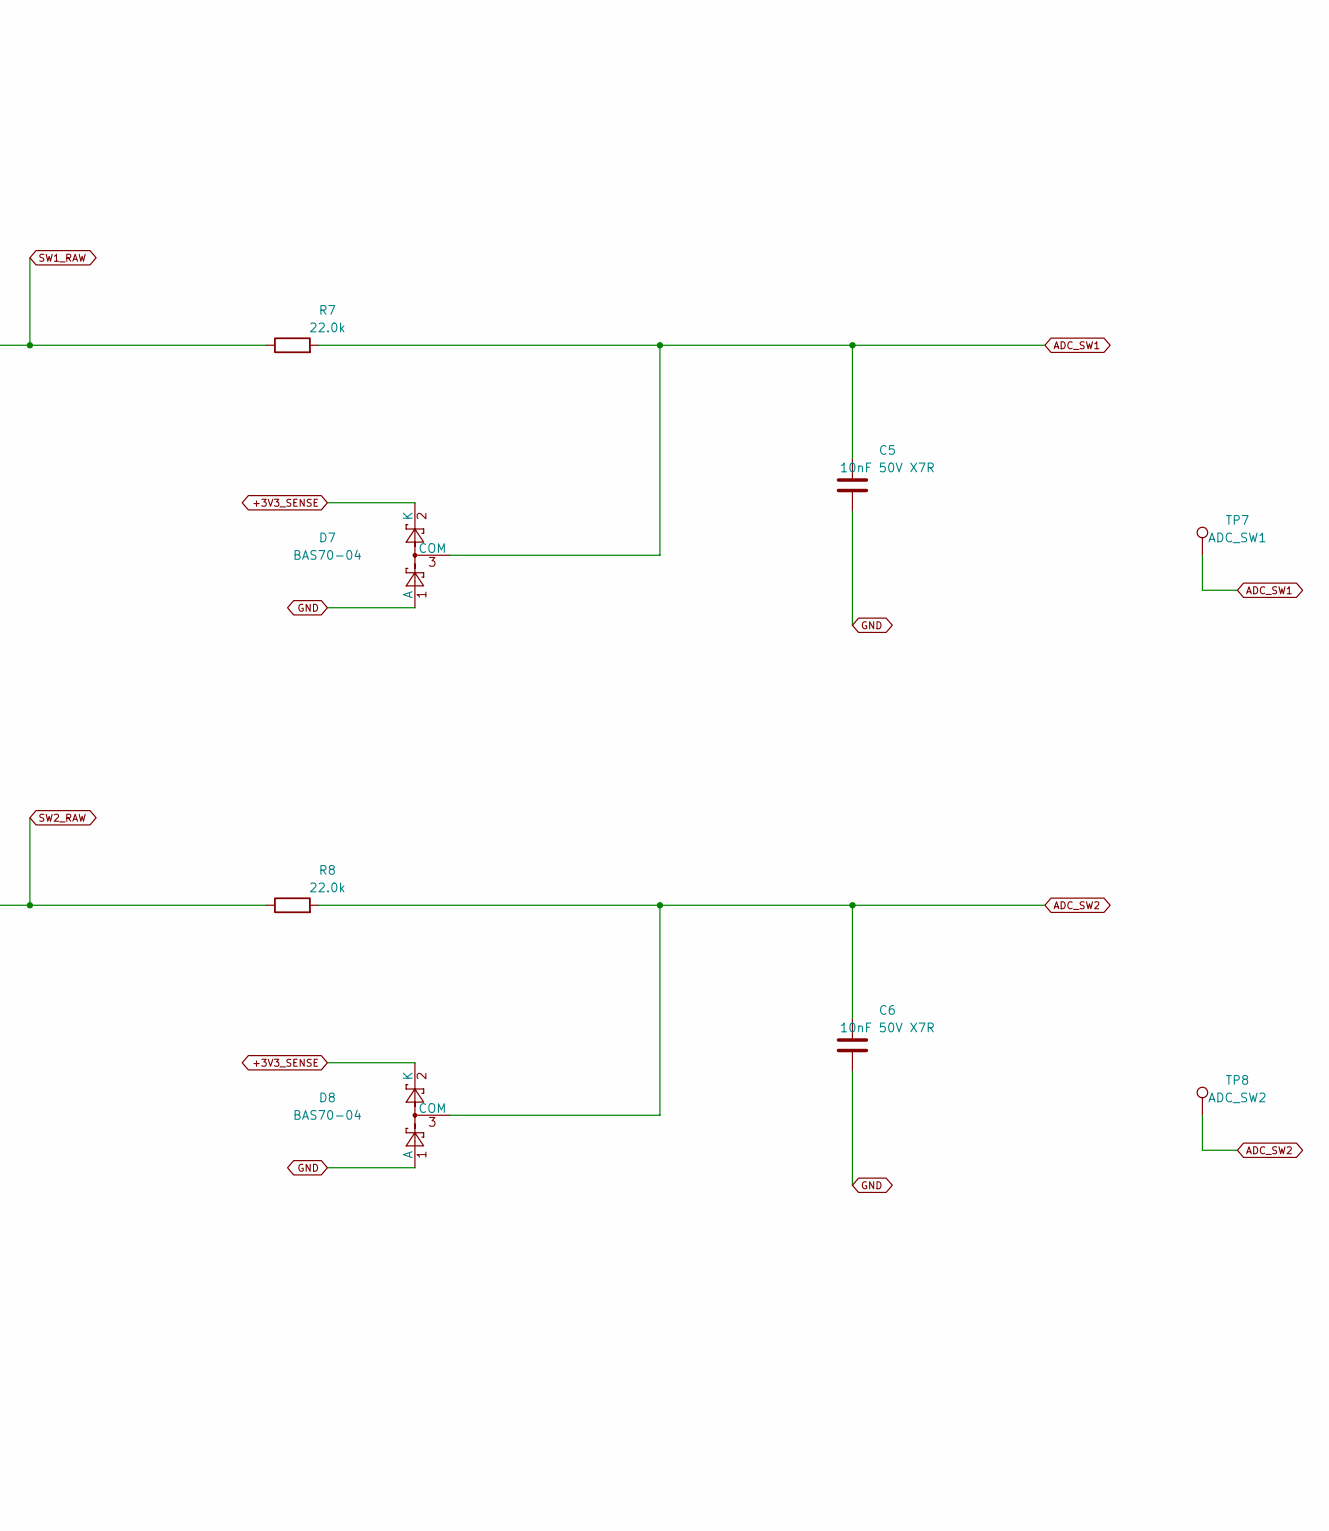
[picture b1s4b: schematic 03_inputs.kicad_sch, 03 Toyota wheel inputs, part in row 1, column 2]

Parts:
C5, C6: 10nF 50V X7R; C_0805_2012Metric; MPN C0805C103K5RACTU
D5, D6: BAS70; SOT-23; MPN BAS70,215
D7, D8: BAS70-04; SOT-23; MPN BAS70-04,215
R5, R6: 2.20k; R_1206_3216Metric; MPN RC1206FR-072K2L
R7, R8: 22.0k; R_0805_2012Metric; MPN RC0805FR-0722KL
TP7: ADC_SW1; TestPoint_Pad_D1.5mm
TP8: ADC_SW2; TestPoint_Pad_D1.5mm

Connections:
+3V3_SENSE: D5.1 (A), D6.1 (A), D7.2 (K), D8.2 (K); also elsewhere on the board
ADC_SW1: C5.1, D7.3 (COM), R7.2, TP7.1; also elsewhere on the board
ADC_SW2: C6.1, D8.3 (COM), R8.2, TP8.1; also elsewhere on the board
GND: C5.2, C6.2, D7.1 (A), D8.1 (A); also elsewhere on the board
unnamed: D5.3 (K), R5.1
unnamed: D6.3 (K), R6.1
SW1_RAW: R5.2, R7.1; also elsewhere on the board
SW2_RAW: R6.2, R8.1; also elsewhere on the board

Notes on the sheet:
03 Toyota wheel inputs
Two identical resistor-ladder inputs. XIAO 3V3 output feeds pull-ups and ADC clamps; ADC reference also3V3. See README for revised bands.
SW1: A0 RC approximately 0.22ms
SW2: A1 RC approximately 0.22ms
SW1: Seek+ <2.5R; Seek- 313-345R; Vol+ 950-1050R; Vol- 2955-3265R. SW2: MODE <2.5R; Hang Up 313-345R; Answer 950-1050R; optional voice band unused. Released: 95-105k on either line. No radio pull-ups may remain connected to SW1/SW2. ADC uses 3V3 reference and 12-bit counts; wheel pull-ups use same 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
